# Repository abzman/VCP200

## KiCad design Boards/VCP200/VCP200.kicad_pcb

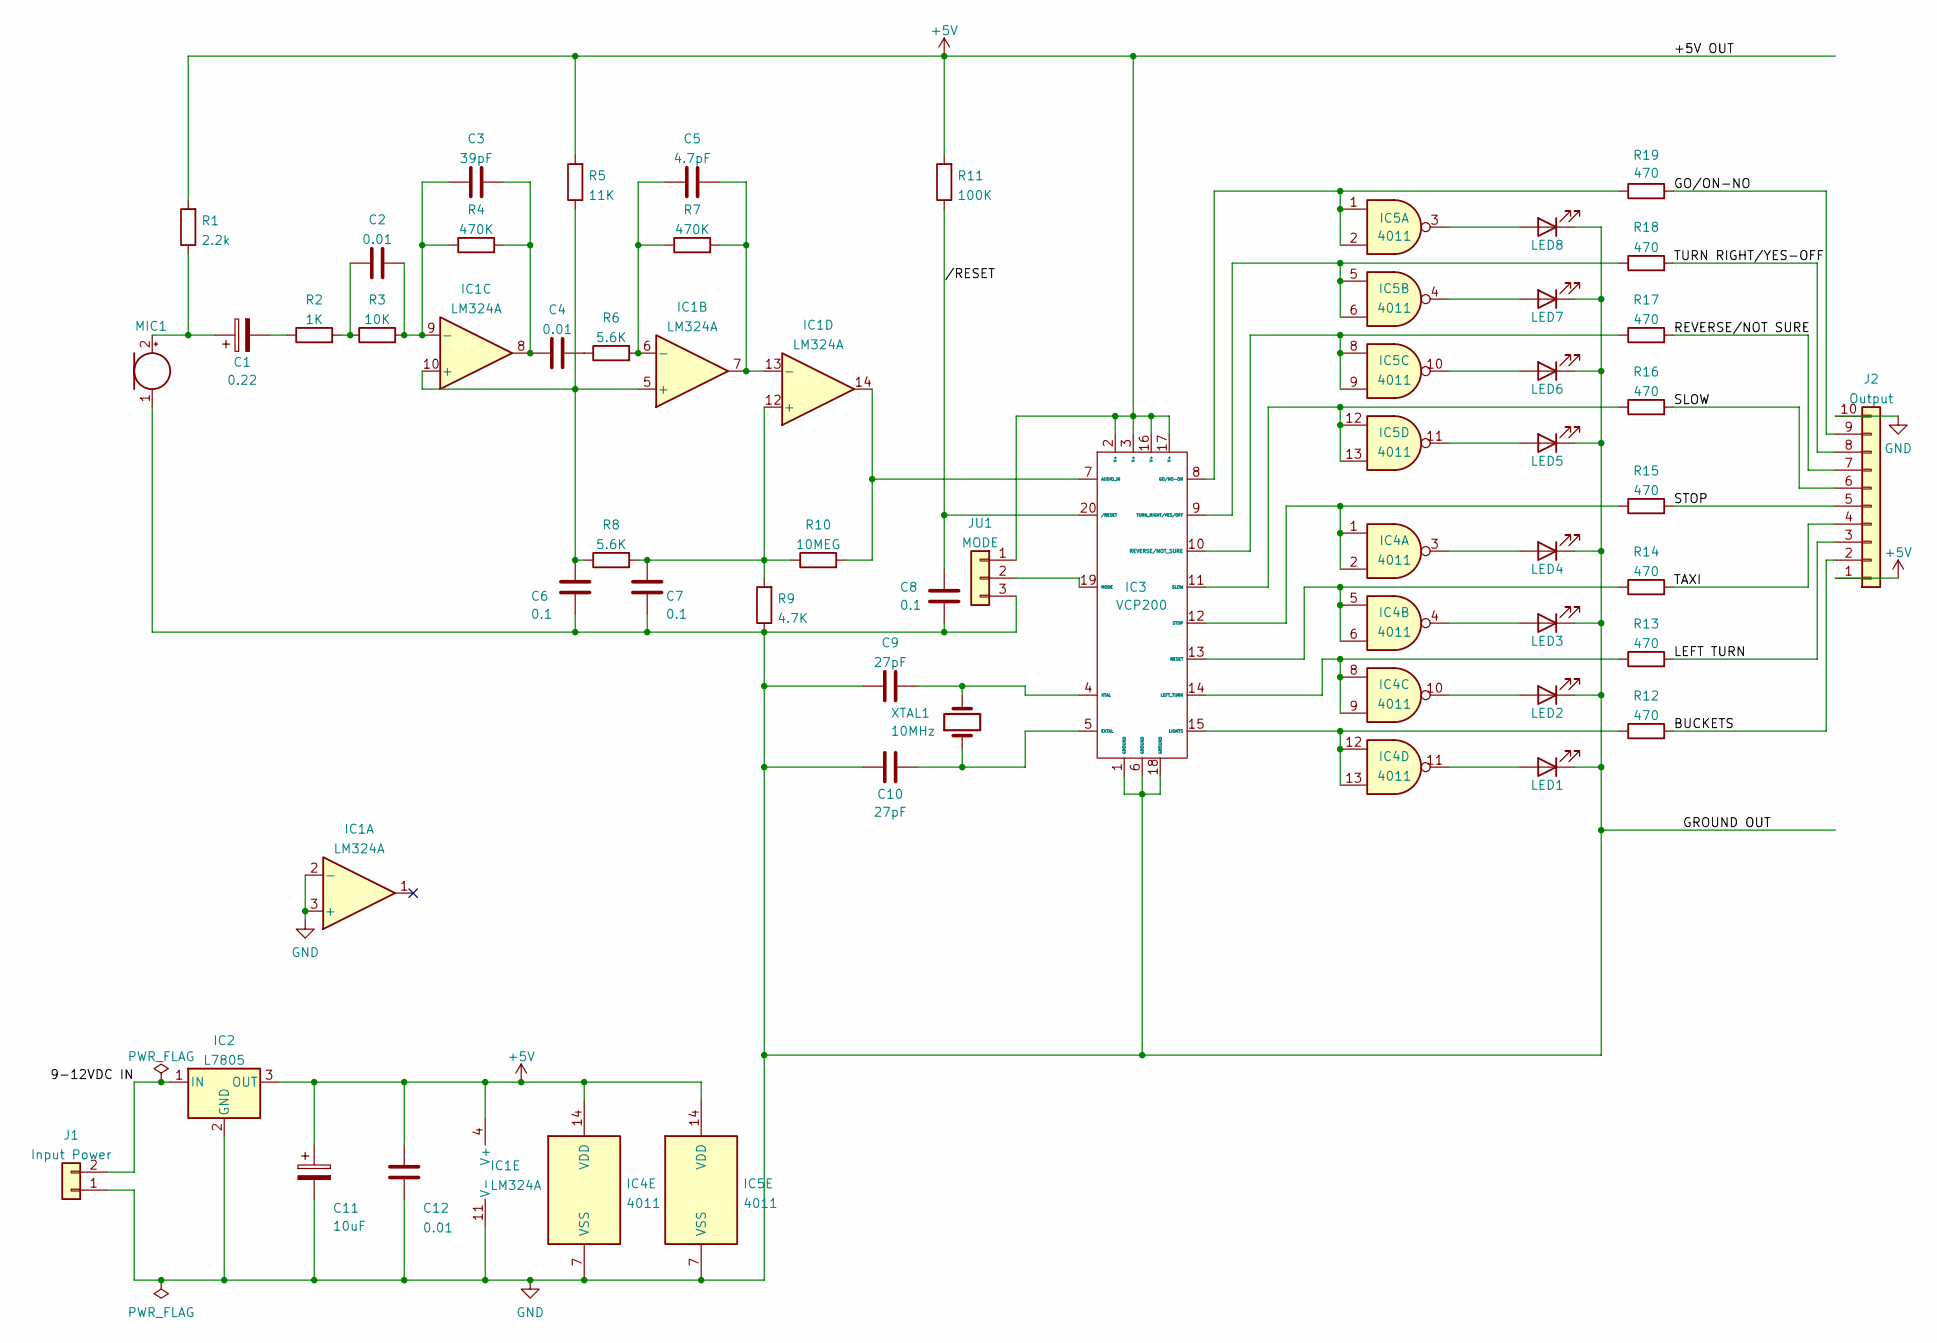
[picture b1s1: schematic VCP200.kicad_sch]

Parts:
C1: 0.22; C_Disc_D4.3mm_W1.9mm_P5.00mm
C2, C4, C12: 0.01; C_Disc_D4.3mm_W1.9mm_P5.00mm
C3: 39pF; C_Disc_D4.3mm_W1.9mm_P5.00mm
C5: 4.7pF; C_Disc_D4.3mm_W1.9mm_P5.00mm
C6, C7, C8: 0.1; C_Disc_D4.3mm_W1.9mm_P5.00mm
C9, C10: 27pF; C_Disc_D4.3mm_W1.9mm_P5.00mm
C11: 10uF; CP_Radial_D5.0mm_P2.00mm
IC1: LM324A; DIP-14_W7.62mm
IC2: L7805; TO-220-3_Horizontal_TabDown
IC3: VCP200; DIP-20_W7.62mm
IC4, IC5: 4011; DIP-14_W7.62mm
J1: Input Power; BarrelJack_GCT_DCJ200-10-A_Horizontal
J2: Output; PinHeader_1x10_P2.54mm_Vertical
JU1: MODE; PinHeader_1x03_P2.54mm_Vertical
LED1, LED2, LED3, LED4, LED5, LED6, LED7, LED8: LED; LED_D5.0mm
MIC1: Microphone; PinHeader_1x02_P2.54mm_Vertical
R1: 2.2k; R_Axial_DIN0207_L6.3mm_D2.5mm_P10.16mm_Horizontal
R2: 1K; R_Axial_DIN0207_L6.3mm_D2.5mm_P10.16mm_Horizontal
R3: 10K; R_Axial_DIN0207_L6.3mm_D2.5mm_P10.16mm_Horizontal
R4, R7: 470K; R_Axial_DIN0207_L6.3mm_D2.5mm_P10.16mm_Horizontal
R5: 11K; R_Axial_DIN0207_L6.3mm_D2.5mm_P10.16mm_Horizontal
R6, R8: 5.6K; R_Axial_DIN0207_L6.3mm_D2.5mm_P10.16mm_Horizontal
R9: 4.7K; R_Axial_DIN0207_L6.3mm_D2.5mm_P10.16mm_Horizontal
R10: 10MEG; R_Axial_DIN0207_L6.3mm_D2.5mm_P10.16mm_Horizontal
R11: 100K; R_Axial_DIN0207_L6.3mm_D2.5mm_P10.16mm_Horizontal
R12, R13, R14, R15, R16, R17, R18, R19: 470; R_Axial_DIN0207_L6.3mm_D2.5mm_P10.16mm_Horizontal
XTAL1: 10MHz; Crystal_HC49-U_Vertical

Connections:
+5V: C11.1, C12.2, IC1.4 (V+), IC2.3 (OUT), IC3.2 (V+), IC3.3 (V+), IC3.16 (V+), IC3.17 (V+), IC4.14 (VDD), IC5.14 (VDD), J2.1, JU1.1, R1.2, R5.2, R11.2
/9-12VDC IN: IC2.1 (IN), J1.2
/BUCKETS: J2.2, R12.2
/GO/ON-NO: J2.9, R19.2
/LEFT TURN: J2.3, R13.2
/RESET: C8.2, IC3.20 (/RESET), R11.1; also elsewhere on the board
/REVERSE/NOT SURE: J2.7, R17.2
/SLOW: J2.6, R16.2
/STOP: J2.5, R15.2
/TAXI: J2.4, R14.2
/TURN RIGHT/YES-OFF: J2.8, R18.2
GND: C6.1, C7.1, C8.1, C9.1, C10.1, C11.2, C12.1, IC1.2 (-), IC1.3 (+), IC1.11 (V-), IC2.2 (GND), IC3.1 (GROUND), IC3.6 (GROUND), IC3.18 (GROUND), IC4.7 (VSS), IC5.7 (VSS), J1.1, J1.3, J2.10, JU1.3, LED1.1 (K), LED2.1 (K), LED3.1 (K), LED4.1 (K), LED5.1 (K), LED6.1 (K), LED7.1 (K), LED8.1 (K), MIC1.1 (-), R9.1
unnamed: C1.2, R2.1
unnamed: C4.2, R6.1
unnamed: C9.2, IC3.4 (XTAL), XTAL1.2
unnamed: C10.2, IC3.5 (EXTAL), XTAL1.1
unnamed: C5.1, IC1.6 (-), R6.2, R7.1
unnamed: C5.2, IC1.7, IC1.13 (-), R7.2
unnamed: C3.2, C4.1, IC1.8, R4.2
unnamed: C2.2, C3.1, IC1.9 (-), R3.2, R4.1
unnamed: C6.2, IC1.5 (+), IC1.10 (+), R5.1, R8.1
unnamed: C7.2, IC1.12 (+), R8.2, R9.2, R10.1
unnamed: IC1.14, IC3.7 (AUDIO_IN), R10.2
unnamed: IC3.19 (MODE), JU1.2
unnamed: IC3.12 (STOP), IC4.1, IC4.2, R15.1
unnamed: IC4.3, LED4.2 (A)
unnamed: IC4.4, LED3.2 (A)
unnamed: IC3.13 (RESET), IC4.5, IC4.6, R14.1
unnamed: IC3.14 (LEFT_TURN), IC4.8, IC4.9, R13.1
unnamed: IC4.10, LED2.2 (A)
unnamed: IC4.11, LED1.2 (A)
unnamed: IC3.15 (LIGHTS), IC4.12, IC4.13, R12.1
unnamed: IC3.8 (GO/NO-ON), IC5.1, IC5.2, R19.1
unnamed: IC3.9 (TURN_RIGHT/YES/OFF), IC5.5, IC5.6, R18.1
unnamed: IC3.10 (REVERSE/NOT_SURE), IC5.8, IC5.9, R17.1
unnamed: IC3.11 (SLOW), IC5.12, IC5.13, R16.1
unnamed: IC5.11, LED5.2 (A)
unnamed: IC5.10, LED6.2 (A)
unnamed: IC5.4, LED7.2 (A)
unnamed: IC5.3, LED8.2 (A)
unnamed: C1.1, MIC1.2 (+), R1.1
unnamed: C2.1, R2.2, R3.1

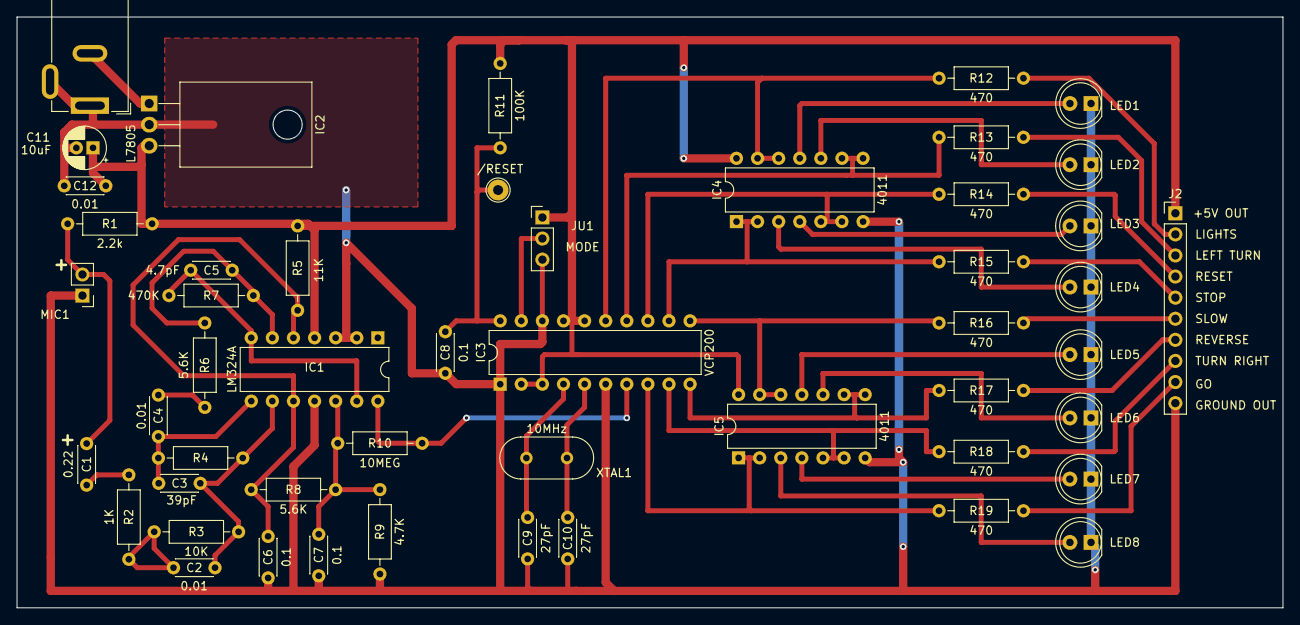
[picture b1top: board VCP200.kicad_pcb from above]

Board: 2 copper layers, 152.4 x 71.1 mm, 50 parts (0 on the bottom side), 42 nets.

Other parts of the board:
/RESET: TestPoint_THTPad_D2.5mm_Drill1.2mm

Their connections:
/RESET: /RESET.1; also elsewhere on the board

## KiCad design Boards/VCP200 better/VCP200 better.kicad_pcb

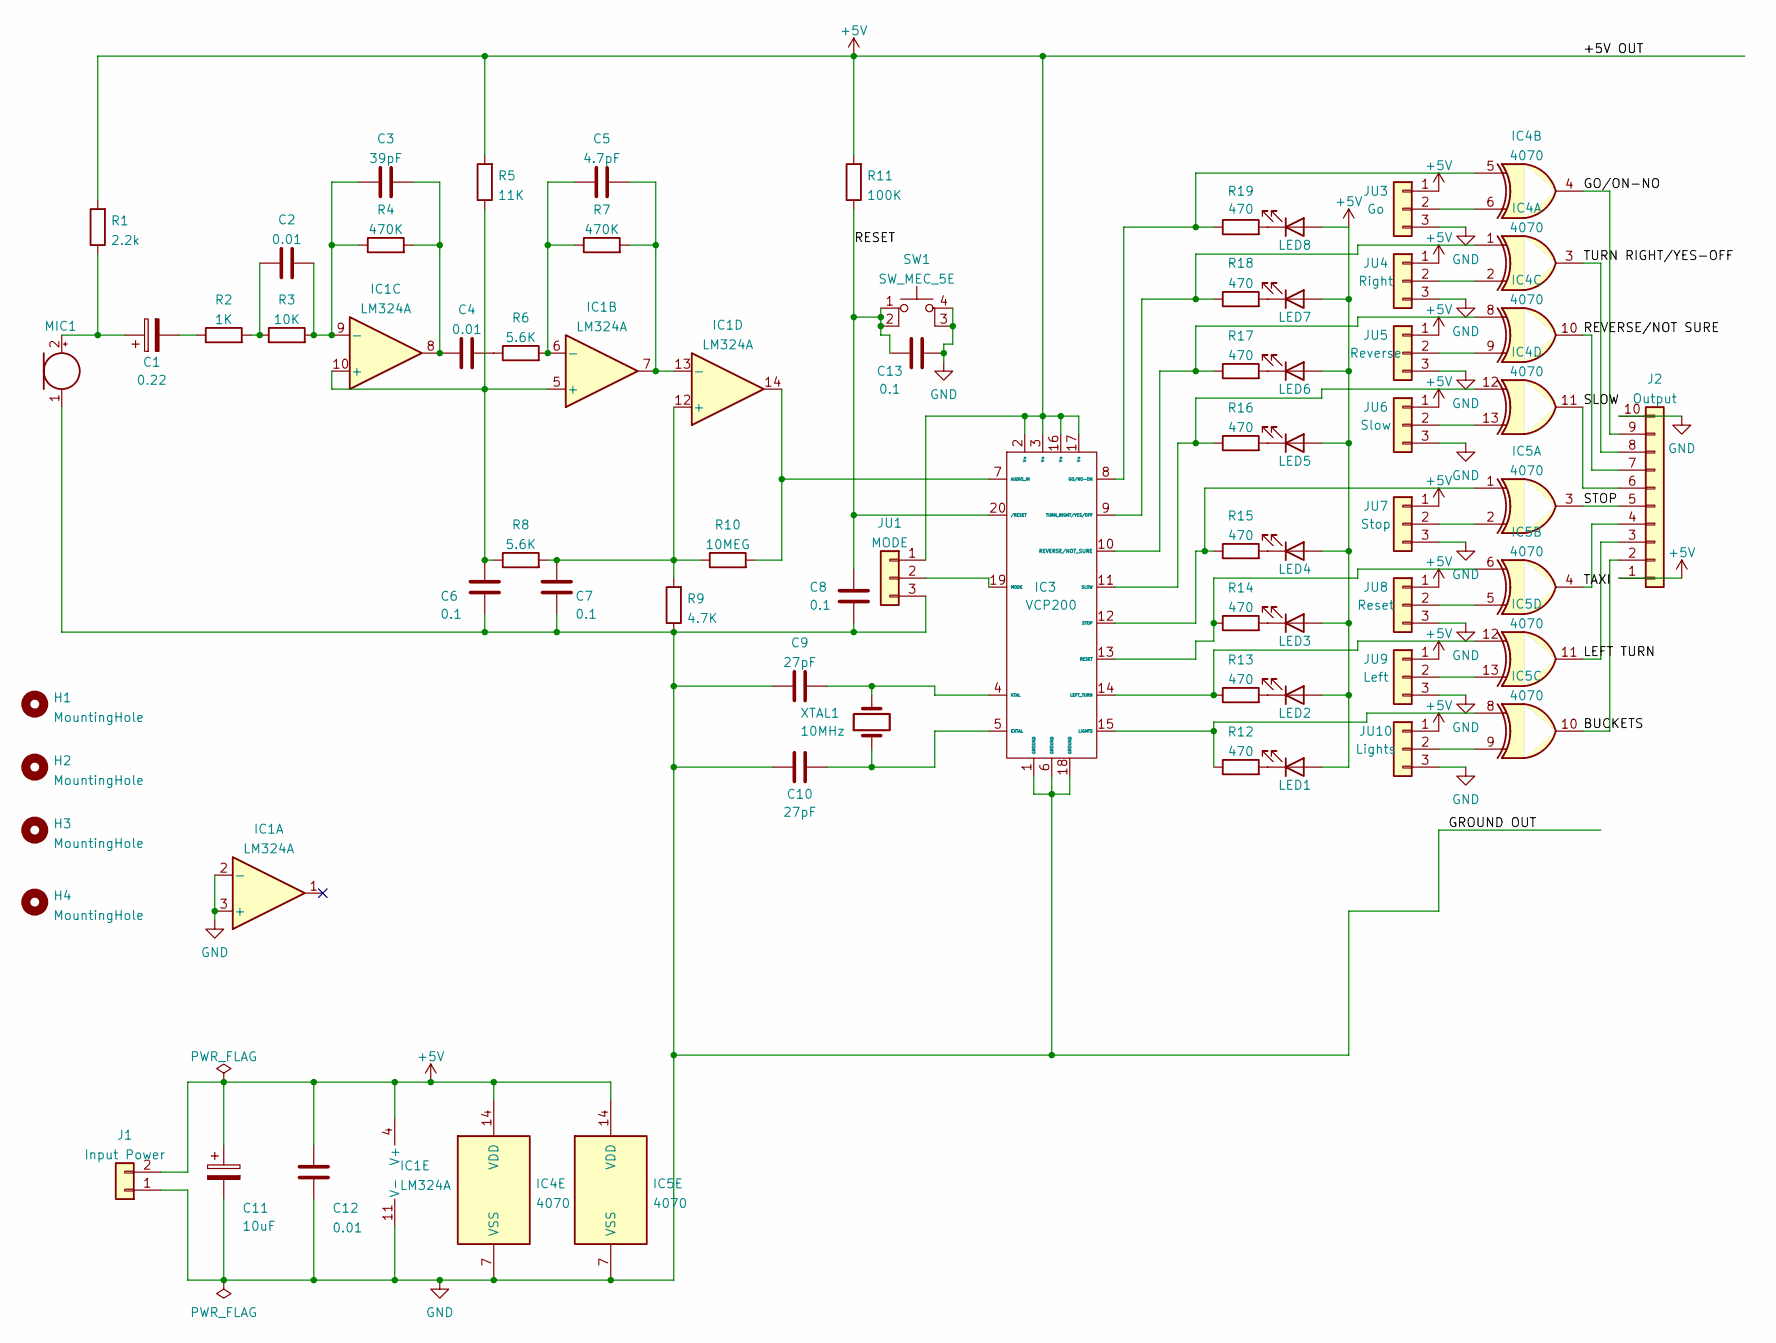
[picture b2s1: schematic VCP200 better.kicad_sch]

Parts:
C1: 0.22; C_Disc_D4.3mm_W1.9mm_P5.00mm
C2, C4, C12: 0.01; C_Disc_D4.3mm_W1.9mm_P5.00mm
C3: 39pF; C_Disc_D4.3mm_W1.9mm_P5.00mm
C5: 4.7pF; C_Disc_D4.3mm_W1.9mm_P5.00mm
C6, C7, C8, C13: 0.1; C_Disc_D4.3mm_W1.9mm_P5.00mm
C9, C10: 27pF; C_Disc_D4.3mm_W1.9mm_P5.00mm
C11: 10uF; CP_Radial_D5.0mm_P2.00mm
H1, H2, H3, H4: MountingHole; MountingHole_3.2mm_M3
IC1: LM324A; DIP-14_W7.62mm
IC3: VCP200; DIP-20_W7.62mm
IC4, IC5: 4070; DIP-14_W7.62mm
J1: Input Power; PinHeader_1x02_P2.54mm_Vertical
J2: Output; PinHeader_1x10_P2.54mm_Vertical
JU1: MODE; PinHeader_1x03_P2.54mm_Vertical
JU3: Go; PinHeader_1x03_P2.54mm_Vertical
JU4: Right; PinHeader_1x03_P2.54mm_Vertical
JU5: Reverse; PinHeader_1x03_P2.54mm_Vertical
JU6: Slow; PinHeader_1x03_P2.54mm_Vertical
JU7: Stop; PinHeader_1x03_P2.54mm_Vertical
JU8: Reset; PinHeader_1x03_P2.54mm_Vertical
JU9: Left; PinHeader_1x03_P2.54mm_Vertical
JU10: Lights; PinHeader_1x03_P2.54mm_Vertical
LED1, LED2, LED3, LED4, LED5, LED6, LED7, LED8: LED; LED_0603_1608Metric
MIC1: Microphone; PinHeader_1x02_P2.54mm_Vertical
R1: 2.2k; R_Axial_DIN0207_L6.3mm_D2.5mm_P10.16mm_Horizontal
R2: 1K; R_Axial_DIN0207_L6.3mm_D2.5mm_P10.16mm_Horizontal
R3: 10K; R_Axial_DIN0207_L6.3mm_D2.5mm_P10.16mm_Horizontal
R4, R7: 470K; R_Axial_DIN0207_L6.3mm_D2.5mm_P10.16mm_Horizontal
R5: 11K; R_Axial_DIN0207_L6.3mm_D2.5mm_P10.16mm_Horizontal
R6, R8: 5.6K; R_Axial_DIN0207_L6.3mm_D2.5mm_P10.16mm_Horizontal
R9: 4.7K; R_Axial_DIN0207_L6.3mm_D2.5mm_P10.16mm_Horizontal
R10: 10MEG; R_Axial_DIN0207_L6.3mm_D2.5mm_P10.16mm_Horizontal
R11: 100K; R_Axial_DIN0207_L6.3mm_D2.5mm_P10.16mm_Horizontal
R12, R13, R14, R15, R16, R17, R18, R19: 470; R_0603_1608Metric
SW1: SW_MEC_5E; SW_TH_Tactile_Omron_B3F-10xx
XTAL1: 10MHz; Crystal_HC49-U_Vertical

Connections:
+5V: C11.1, C12.2, IC1.4 (V+), IC3.2 (V+), IC3.3 (V+), IC3.16 (V+), IC3.17 (V+), IC4.14 (VDD), IC5.14 (VDD), J1.2, J2.1, JU1.1, JU3.1, JU4.1, JU5.1, JU6.1, JU7.1, JU8.1, JU9.1, JU10.1, LED1.2 (A), LED2.2 (A), LED3.2 (A), LED4.2 (A), LED5.2 (A), LED6.2 (A), LED7.2 (A), LED8.2 (A), R1.2, R5.2, R11.2
/BUCKETS: IC5.10, J2.2
/GO/ON-NO: IC4.4, J2.9
/LEFT TURN: IC5.11, J2.3
/RESET: C8.2, C13.1, IC3.20 (/RESET), R11.1, SW1.1, SW1.2; also elsewhere on the board
/REVERSE/NOT SURE: IC4.10, J2.7
/SLOW: IC4.11, J2.6
/STOP: IC5.3, J2.5
/TAXI: IC5.4, J2.4
/TURN RIGHT/YES-OFF: IC4.3, J2.8
GND: C6.1, C7.1, C8.1, C9.1, C10.1, C11.2, C12.1, C13.2, IC1.2 (-), IC1.3 (+), IC1.11 (V-), IC3.1 (GROUND), IC3.6 (GROUND), IC3.18 (GROUND), IC4.7 (VSS), IC5.7 (VSS), J1.1, J2.10, JU1.3, JU3.3, JU4.3, JU5.3, JU6.3, JU7.3, JU8.3, JU9.3, JU10.3, MIC1.1 (-), R9.1, SW1.3 (K), SW1.4 (A)
unnamed: C1.1, MIC1.2 (+), R1.1
unnamed: C1.2, R2.1
unnamed: C2.1, R2.2, R3.1
unnamed: C2.2, C3.1, IC1.9 (-), R3.2, R4.1
unnamed: C3.2, C4.1, IC1.8, R4.2
unnamed: C4.2, R6.1
unnamed: C5.1, IC1.6 (-), R6.2, R7.1
unnamed: C5.2, IC1.7, IC1.13 (-), R7.2
unnamed: C6.2, IC1.5 (+), IC1.10 (+), R5.1, R8.1
unnamed: C7.2, IC1.12 (+), R8.2, R9.2, R10.1
unnamed: C9.2, IC3.4 (XTAL), XTAL1.2
unnamed: C10.2, IC3.5 (EXTAL), XTAL1.1
unnamed: IC1.14, IC3.7 (AUDIO_IN), R10.2
unnamed: IC3.8 (GO/NO-ON), IC4.5, R19.1
unnamed: IC3.9 (TURN_RIGHT/YES/OFF), IC4.1, R18.1
unnamed: IC3.10 (REVERSE/NOT_SURE), IC4.8, R17.1
unnamed: IC3.11 (SLOW), IC4.12, R16.1
unnamed: IC3.12 (STOP), IC5.1, R15.1
unnamed: IC3.13 (RESET), IC5.6, R14.1
unnamed: IC3.14 (LEFT_TURN), IC5.12, R13.1
unnamed: IC3.15 (LIGHTS), IC5.8, R12.1
unnamed: IC3.19 (MODE), JU1.2
unnamed: IC4.2, JU4.2
unnamed: IC4.6, JU3.2
unnamed: IC4.9, JU5.2
unnamed: IC4.13, JU6.2
unnamed: IC5.2, JU7.2
unnamed: IC5.5, JU8.2
unnamed: IC5.9, JU10.2
unnamed: IC5.13, JU9.2
unnamed: LED1.1 (K), R12.2
unnamed: LED2.1 (K), R13.2
unnamed: LED3.1 (K), R14.2
unnamed: LED4.1 (K), R15.2
unnamed: LED5.1 (K), R16.2
unnamed: LED6.1 (K), R17.2
unnamed: LED7.1 (K), R18.2
unnamed: LED8.1 (K), R19.2

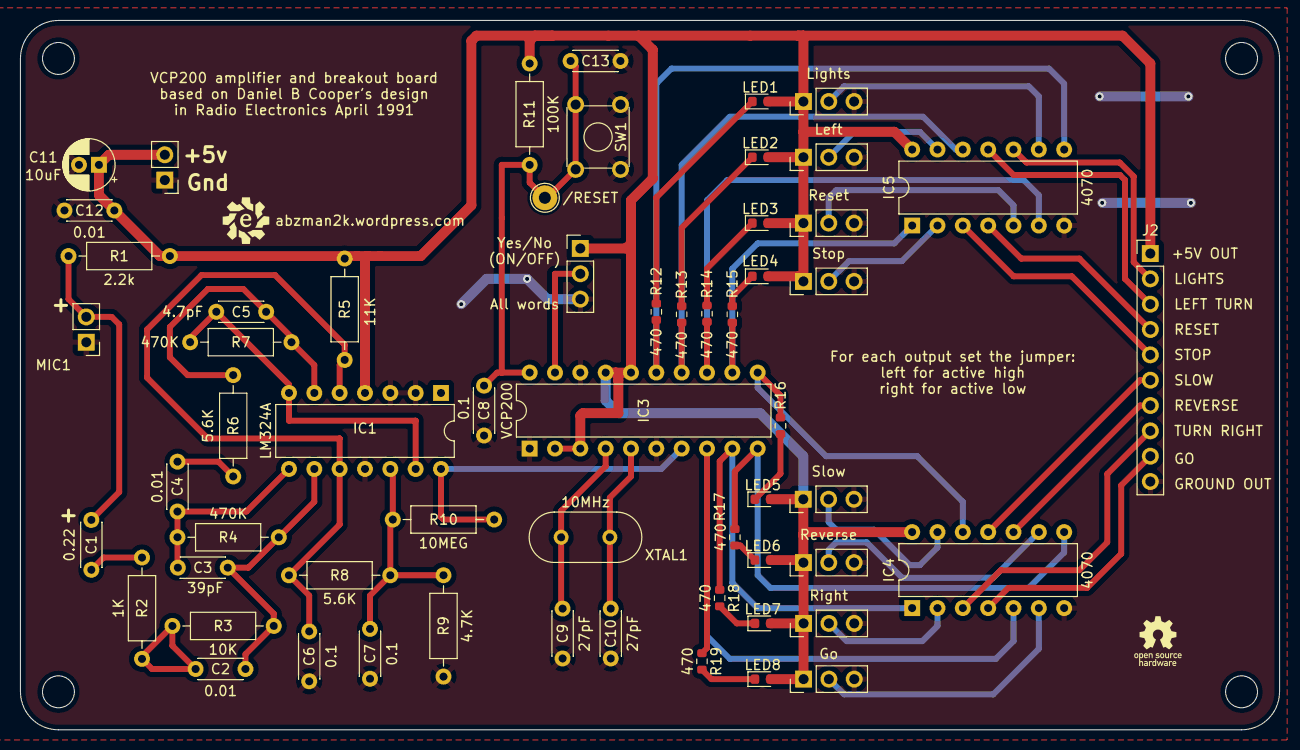
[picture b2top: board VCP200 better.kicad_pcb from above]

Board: 2 copper layers, 126.2 x 71.1 mm, 63 parts (0 on the bottom side), 49 nets.

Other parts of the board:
/RESET: TestPoint_THTPad_D2.5mm_Drill1.2mm

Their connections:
/RESET: /RESET.1; also elsewhere on the board

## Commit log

2023-11-03 added boards for using vcp200
